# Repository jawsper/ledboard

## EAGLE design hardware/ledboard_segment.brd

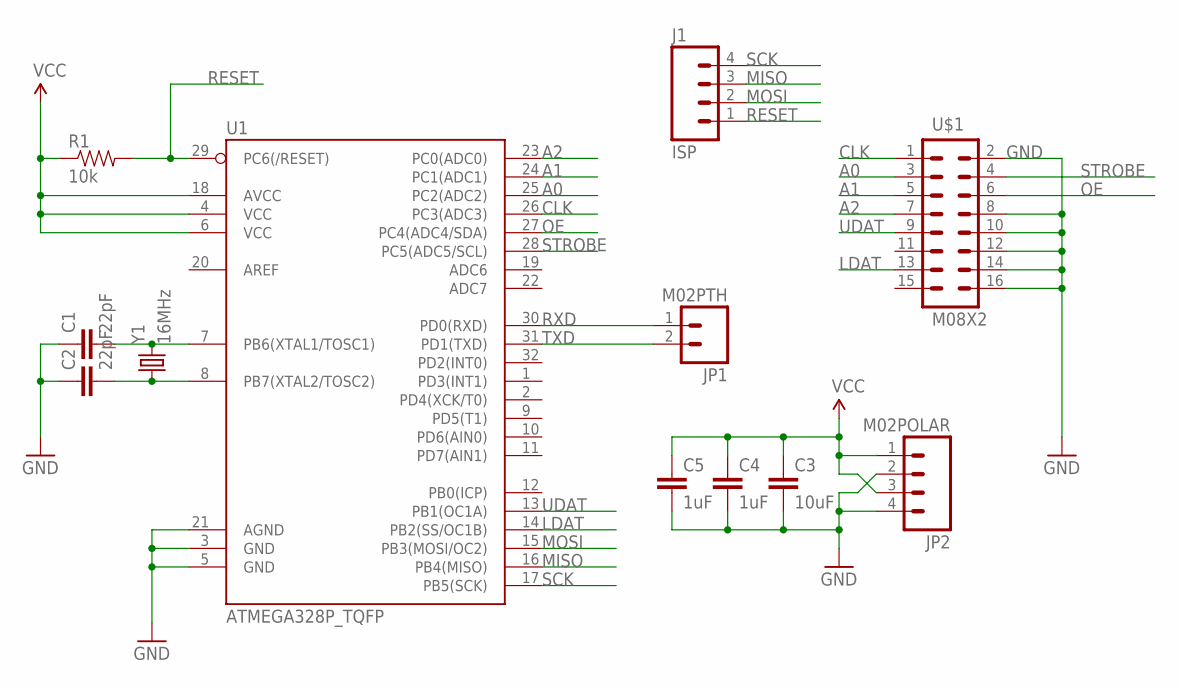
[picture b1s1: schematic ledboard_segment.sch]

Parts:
C1, C2: 22pF; 0805
C3: 10uF; 0805
C4, C5: 1uF; 0805
J1: ISP; 1X04
JP1: M02PTH; 1X02
JP2: M02POLAR; 1X04_NO_SILK
R1: 10k; 0805
U1: ATMEGA328P_TQFP; TQFP32-08
U$1: M08X2; 2X8
Y1: 16MHz; CRYSTAL-TXC-7A

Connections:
A0: U1.25 (PC2(ADC2)), U$1.3
A1: U1.24 (PC1(ADC1)), U$1.5
A2: U1.23 (PC0(ADC0)), U$1.7
CLK: U1.26 (PC3(ADC3)), U$1.1
GND: C1.1, C2.1, C3.2, C4.2, C5.2, JP2.2, JP2.4, U1.3 (GND), U1.5 (GND), U1.21 (AGND), U$1.2, U$1.8, U$1.10, U$1.12, U$1.14, U$1.16
LDAT: U1.14 (PB2(SS/OC1B)), U$1.13
MISO: J1.3, U1.16 (PB4(MISO))
MOSI: J1.2, U1.15 (PB3(MOSI/OC2))
OE: U1.27 (PC4(ADC4/SDA)), U$1.6
RESET: J1.1, R1.2, U1.29 (PC6(/RESET))
RXD: JP1.1, U1.30 (PD0(RXD))
SCK: J1.4, U1.17 (PB5(SCK))
STROBE: U1.28 (PC5(ADC5/SCL)), U$1.4
TXD: JP1.2, U1.31 (PD1(TXD))
UDAT: U1.13 (PB1(OC1A)), U$1.9
VCC: C3.1, C4.1, C5.1, JP2.1, JP2.3, R1.1, U1.4 (VCC), U1.6 (VCC), U1.18 (AVCC)
XTAL1: C1.2, U1.7 (PB6(XTAL1/TOSC1)), Y1.P$2 (2)
XTAL2: C2.2, U1.8 (PB7(XTAL2/TOSC2)), Y1.P$1 (1)

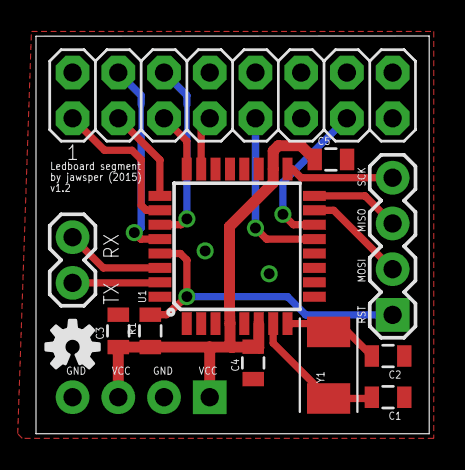
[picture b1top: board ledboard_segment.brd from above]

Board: 2 copper layers, 21.8 x 22.1 mm, 13 parts (0 on the bottom side), 18 nets.

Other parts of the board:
U$2: OSHW-LOGO-S

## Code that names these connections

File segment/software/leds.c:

/*
Support routine for the 32x16 led-board as sold by Baco Army Goods.
(C) 2008 Jeroen Domburg (jeroen AT spritesmods.com)

This program is free software: you can redistribute it and/or modify
t under the terms of the GNU General Public License as published by
the Free Software Foundation, either version 3 of the License, or
(at your option) any later version.
        
This program is distributed in the hope that it will be useful,
but WITHOUT ANY WARRANTY; without even the implied warranty of
MERCHANTABILITY or FITNESS FOR A PARTICULAR PURPOSE.  See the
GNU General Public License for more details.
                
You should have received a copy of the GNU General Public License
along with this program.  If not, see <http://www.gnu.org/licenses/>.
*/

// CLK |     A0 | A1 |  A2 | UDAT | NC  | LDAT |  NC
// 1   |      3 |  5 |   7 |    9 |  11 |   13 |  15
// 2   |      4 |  6 |   8 |   10 |  12 |   14 |  16
// GND | STROBE | OE | GND |  GND | GND |  GND | GND

//Pinout of the led-board:
//1: CLK
//2: GND
//3: A0
//4: STROBE
//5: A1
//6: OE
//7: A2
//8: GND
//9: UDAT (upper pixel data)
//10: GND
//11: NC
//12: GND
//13: LDAT (lower pixel data)
//14: GND
//15: NC
//16: GND
//
//J1 is data in (to which the microcontroller must be soldered), J2
//is data out (which is unused here).

#include "leds.h"
#include <avr/io.h>
#include <avr/interrupt.h>
#include <util/delay.h>

//IO-ports
//If you change the port itself (e.g. PB0->PD0) you'll have to
//track down these ports in the rest of the code too.
#define A2 PC0
#define PORT_A2 PORTC

#define A1 PC1
#define PORT_A1 PORTC

#define A0 PC2
#define PORT_A0 PORTC

#define CLK PC3
#define PORT_CLK PORTC

#define OE PC4
#define PORT_OE PORTC

#define STROBE PC5
#define PORT_STROBE PORTC

#define UDAT PB1
#define PORT_UDAT PORTB

#define LDAT PB2
#define PORT_LDAT PORTB

//Display memory. The main routine can write here to modify the image on the 
//LED-board. 0 = black = led completely off, 255 = 'white' = led completely on.
unsigned char dispmem[512];

//Initialize led-board-driver
void initleds(void)
{
//Pin direction
    DDRB = (1 << UDAT) | (1 << LDAT);
    DDRC = (1 << CLK) | (1 << A0) | (1 << A1) | (1 << A2) | (1 << STROBE) | (1 << OE);
//Timer for ledboard row advance interrupt.
//Any timer can be used for this, as long as its interrupt routine
//calls the ISR with a speed of at least 13KHz.
    // TCCR1A = 0;
    // TCCR1B = 9; //CTC, no prescaler
    // OCR1A = (F_CPU / (800 * 8));
    // TIMSK1=2; //OCIE1A int enable
}

//Timer interrupts. Sends the next row of pixels to the LCD.

//This routine has grayscale-support: it tries to PWM each pixel
//to let the mean of the duty-cycle be the value in the dispmem-array.
//To reduce flickering, the phase of the pwm-signal is inverted every pixel,
//every row and every frame. so each pixel will flicker out of sync with the
//pixels above, beneath, left from and right from it. This'll immensely reduce
//the perception of flickering, so the 'real' framerate can be much lower than
//the one required for flicker-free b/w images.


//GRAYINC will adjust the precision of the routines. If GRAYINC is
//(1<<n), the precision will be (8-n) bits. The advantage of a lower precision
//is that the frame rate can be turned down. (1<<3) is the limit for an
//ATMega88 at 20MHz and gives 5-bit precision.
#define GRAYINC (1 << 3)

void do_leds()
// ISR(TIMER1_COMPA_vect)
{
    static char rowno; //number of the row we're at now
    static unsigned char *posu,*posd; //position in display memory
    static unsigned char comp; //compare-value for grayscales
    char x;

    //Send next line    
    PORT_STROBE &= ~(1 << STROBE); //disable strobe in advance
    for(x=0; x<32; x++) //for each pixel:
    {
        PORT_UDAT &= ~(1 << UDAT);
        PORT_LDAT &= ~(1 << LDAT); //clear data inputs
        PORT_CLK &= ~(1 << CLK); //reset clock in advance
        if(*posu > comp) PORT_UDAT |= (1<<UDAT); //if pixel should be shown, set output
        if(*posd > comp) PORT_LDAT |= (1<<LDAT); //same for the lower 8 rows
        posu++; posd++; //next memory position
        PORT_CLK |= (1 << CLK); //clock in the bits
        comp += 128; //invert phase of pwm every pixel
    }
    comp += 128; //invert phase of pwm every row too


    PORT_OE |= (1 << OE); //disable led output
    PORT_STROBE |= (1 << STROBE); //latch in the led values
    //select correct row
    PORT_A0 &= ~((1 << A0) | (1 << A1) | (1 << A2));
    if(rowno & 1) PORT_A0 |= (1 << A0);
    if(rowno & 2) PORT_A1 |= (1 << A1);
    if(rowno & 4) PORT_A2 |= (1 << A2);
    PORT_OE &= ~(1 << OE); //enable led output
    rowno++; //Ok, this row is done.
    if(rowno > 7) //Frame done?
    {
        rowno = 0; //reset row count
        posu = dispmem;
        posd = dispmem + 256; //reset memory pos
        comp += 128 + GRAYINC; //invert phase of pwm and increase
    }
}

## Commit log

2015-01-04 Eagle files
2015-01-04 Add sprite_tm's modified ledmatrix code.
2015-01-04 Move segment hard+software to folder
2015-01-04 Add controller code.
2015-01-04 Add controller schematics.
2015-01-05 Made board 10 mil smaller + minor tweaks
    Some prettification of traces.
2015-01-05 Some visual tweaks.
2015-01-15 Moved dimensions to correct layer.
2015-01-27 Minor tweaks, board version 1.2
2015-01-27 Fixed baudrate
2015-01-27 Made code easier to read, decreased precision.
2015-01-27 Switched to avrisp programmer...
2015-11-26 Added teensy version of the controller software. Features new protocol.
2015-11-26 Added info how to connect teensy to ethernet.
2015-11-27 Fix output bug, add brightness to drawString, add debug option.
2015-12-01 Added ledmatrix simulator
2016-03-24 also included rpi version of controller software
2016-03-24 removed binary
2016-03-24 rename rpi folder to sprite_ledboard_rpi to prevent future confusion when software will be written for different raspbery pi's with maybe different displays

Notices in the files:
parts and their libraries:
SparkFun-Connectors: Licensing: Creative Commons ShareAlike 4.0 International - https://creativecommons.org/licenses/by-sa/4.0
